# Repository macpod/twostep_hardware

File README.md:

twostep_hardware
================

TwoStep stepper motor controller board

More general and purchasing information is avaliable here:
http://macpod.net/electronics/twostep/twostep.php

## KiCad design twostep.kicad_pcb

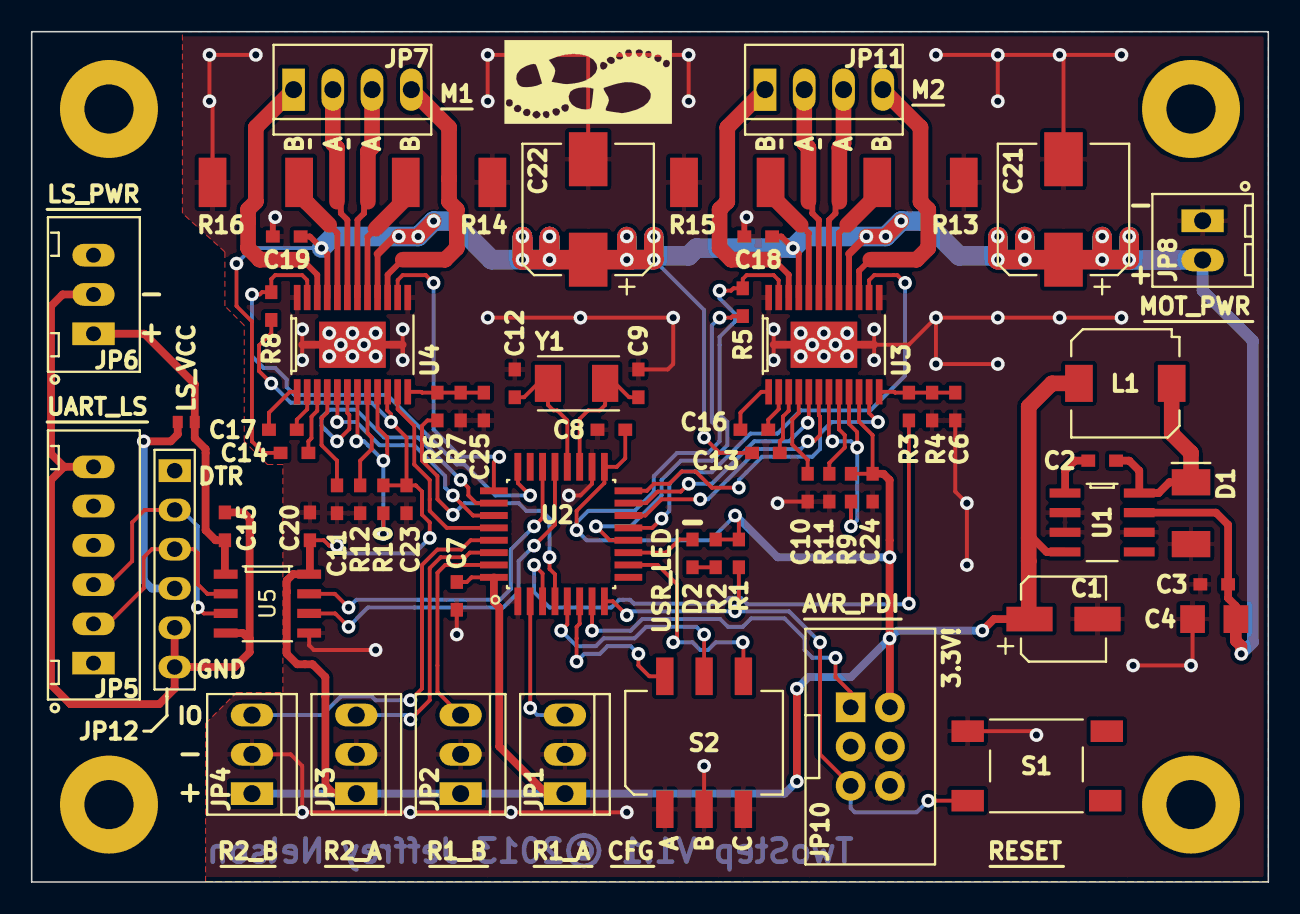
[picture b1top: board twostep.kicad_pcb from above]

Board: 2 copper layers, 80.0 x 55.0 mm, 68 parts (0 on the bottom side), 63 nets.

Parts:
C1: 10uF; UUD1V100MCL1GS
C2: 10000pF; 0603
C3, C7, C8, C13, C14, C15, C16, C17, C18, C19, C20, C23, C24: 0.1uF; 0603
C4: 1uF; 1206
C6, C25: NP; 0603
C9, C12: 15pF; 0603
C10, C11: 0.22uF; 0603
C21, C22: 100uF; UCW1H101MNL1GS
D1: B160-13-F
D2: USR_LED; LED_0603
G1: TWOSTEP_LOGO
JP1: R1_A; 0022272031
JP2: R1_B; 0022272031
JP3: R2_A; 0022272031
JP4: R2_B; 0022272031
JP5: UART_LS; JST-XH-6
JP6: LS_PWR; JST-XH-3
JP7: M1; 0022272041
JP8: MOT_PWR; 282834-2
JP10: AVR_PDI
JP11: M2; 0022272041
JP12: UART_FTDI; HEADER_2_54X6
JP13: LS_VCC; 0603_JUMPER
L1: 470uH; SRR7045-471M
MP1, MP2, MP3, MP4: STANDOFF; 4-40MountHole
R1, R3, R4, R5, R6, R7, R8, R9, R10, R11, R12: 10K; 0603
R2: 1K; 0603
R13, R14, R15, R16: 0.05; 2512
S1: RESET; 3-1437565-0
S2: CFG; 219-3MST
U1: LM2674MX-3.3
U2: ATXMEGA16E5-AU
U3, U4: A4982; A4982SLPTR-T
U5: SI8621; SI8621BC-B-IS
Y1: 16Mhz; 7A-16.000MAHE-T

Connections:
+3.3V: C1.1, C7.2, C8.2, C20.2, C23.2, C24.2, JP1.1, JP2.1, JP3.1, JP4.1, JP10.2, L1.1, R1.2, R2.2, R5.2, R8.2, R9.2, R10.2, U1.4, U2.17, U2.32, U3.10, U4.10, U5.8
/CFG_0: S2.6, U2.6
/CFG_1: S2.5, U2.5
/CFG_2: S2.4, U2.10
/DAC_0: R6.2, U2.4
/DAC_1: R3.2, U2.3
/DIR_1: U2.25, U4.14
/DIR_2: U2.13, U3.14
/ENABLE_1: R8.1, U2.24, U4.23
/ENABLE_2: R5.1, U2.12, U3.23
/LS_RXI: JP5.3, JP12.2, U5.3
/LS_TXO: JP5.2, JP12.3, U5.2
/MS1_1: U2.27, U4.5
/MS1_2: U2.15, U3.5
/MS2_1: U2.26, U4.6
/MS2_2: U2.14, U3.6
/OUT1A_1: JP7.3, U4.18
/OUT1A_2: JP11.3, U3.18
/OUT1B_1: JP7.4, U4.15
/OUT1B_2: JP11.4, U3.15
/OUT2A_1: JP7.2, U4.19
/OUT2A_2: JP11.2, U3.19
/OUT2B_1: JP7.1, U4.22
/OUT2B_2: JP11.1, U3.22
/PDI_CLK: JP10.5, R1.1, S1.3, U2.8
/PDI_DATA: JP10.1, U2.7
/R1_A: JP1.3, U2.2
/R1_B: JP2.3, U2.31
/R2_A: JP3.3, U2.30
/R2_B: JP4.3, U2.29
/REF_1: C25.2, R6.1, R7.2, U4.12
/REF_2: C6.2, R3.1, R4.2, U3.12
/STEP_1: U2.28, U4.11
/STEP_2: U2.16, U3.11
/TS_RXI: U2.22, U5.7
/TS_TXO: U2.21, U5.6
/USR_LED: D2.2, U2.11
GND: C1.2, C3.1, C4.1, C6.1, C7.1, C8.1, C9.1, C10.1, C11.1, C12.1, C18.1, C19.1, C20.1, C21.2, C22.2, C23.1, C24.1, C25.1, D1.1, JP1.2, JP2.2, JP3.2, JP4.2, JP8.1, JP10.6, R4.1, R7.1, R11.1, R12.1, R13.1, R14.1, R15.1, R16.1, S1.1, S2.1, S2.2, S2.3, U1.2, U1.3, U1.6, U2.1, U2.18, U3.13, U3.24, U3.25, U4.13, U4.24, U4.25, U5.5
LS_GND: C15.1, JP5.6, JP6.2, JP12.5, JP12.6, U5.4
LS_VCC: C15.2, JP6.1, JP13.2, U5.1
MOT_VCC: C3.2, C4.2, C13.2, C14.2, C18.2, C19.2, C21.1, C22.1, JP8.2, U1.7, U3.16, U3.21, U4.16, U4.21
unnamed: C9.2, U2.19, Y1.1
unnamed: C10.2, U3.4
unnamed: C13.1, U3.3
unnamed: R9.1, U3.7, U3.9
unnamed: C16.1, U3.2
unnamed: C16.2, U3.1
unnamed: R13.2, U3.17
unnamed: R11.2, U3.8
unnamed: R15.2, U3.20
unnamed: C12.2, U2.20, Y1.2
unnamed: C2.1, D1.2, L1.2, U1.8
unnamed: C2.2, U1.1
unnamed: R14.2, U4.17
unnamed: C14.1, U4.3
unnamed: JP12.4, JP13.1
unnamed: R12.2, U4.8
unnamed: R10.1, U4.7, U4.9
unnamed: R16.2, U4.20
unnamed: D2.1, R2.1
unnamed: C11.2, U4.4
unnamed: C17.1, U4.2
unnamed: C17.2, U4.1

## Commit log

2014-01-02 Initial commit of twostep pcb
2014-01-10 adding twostep brd file

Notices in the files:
twostep.kicad_pcb:
Creative Commons Attribution-ShareAlike 4.0 International License
TwoStep V1.1 ©2013 Jeffrey Nelson
